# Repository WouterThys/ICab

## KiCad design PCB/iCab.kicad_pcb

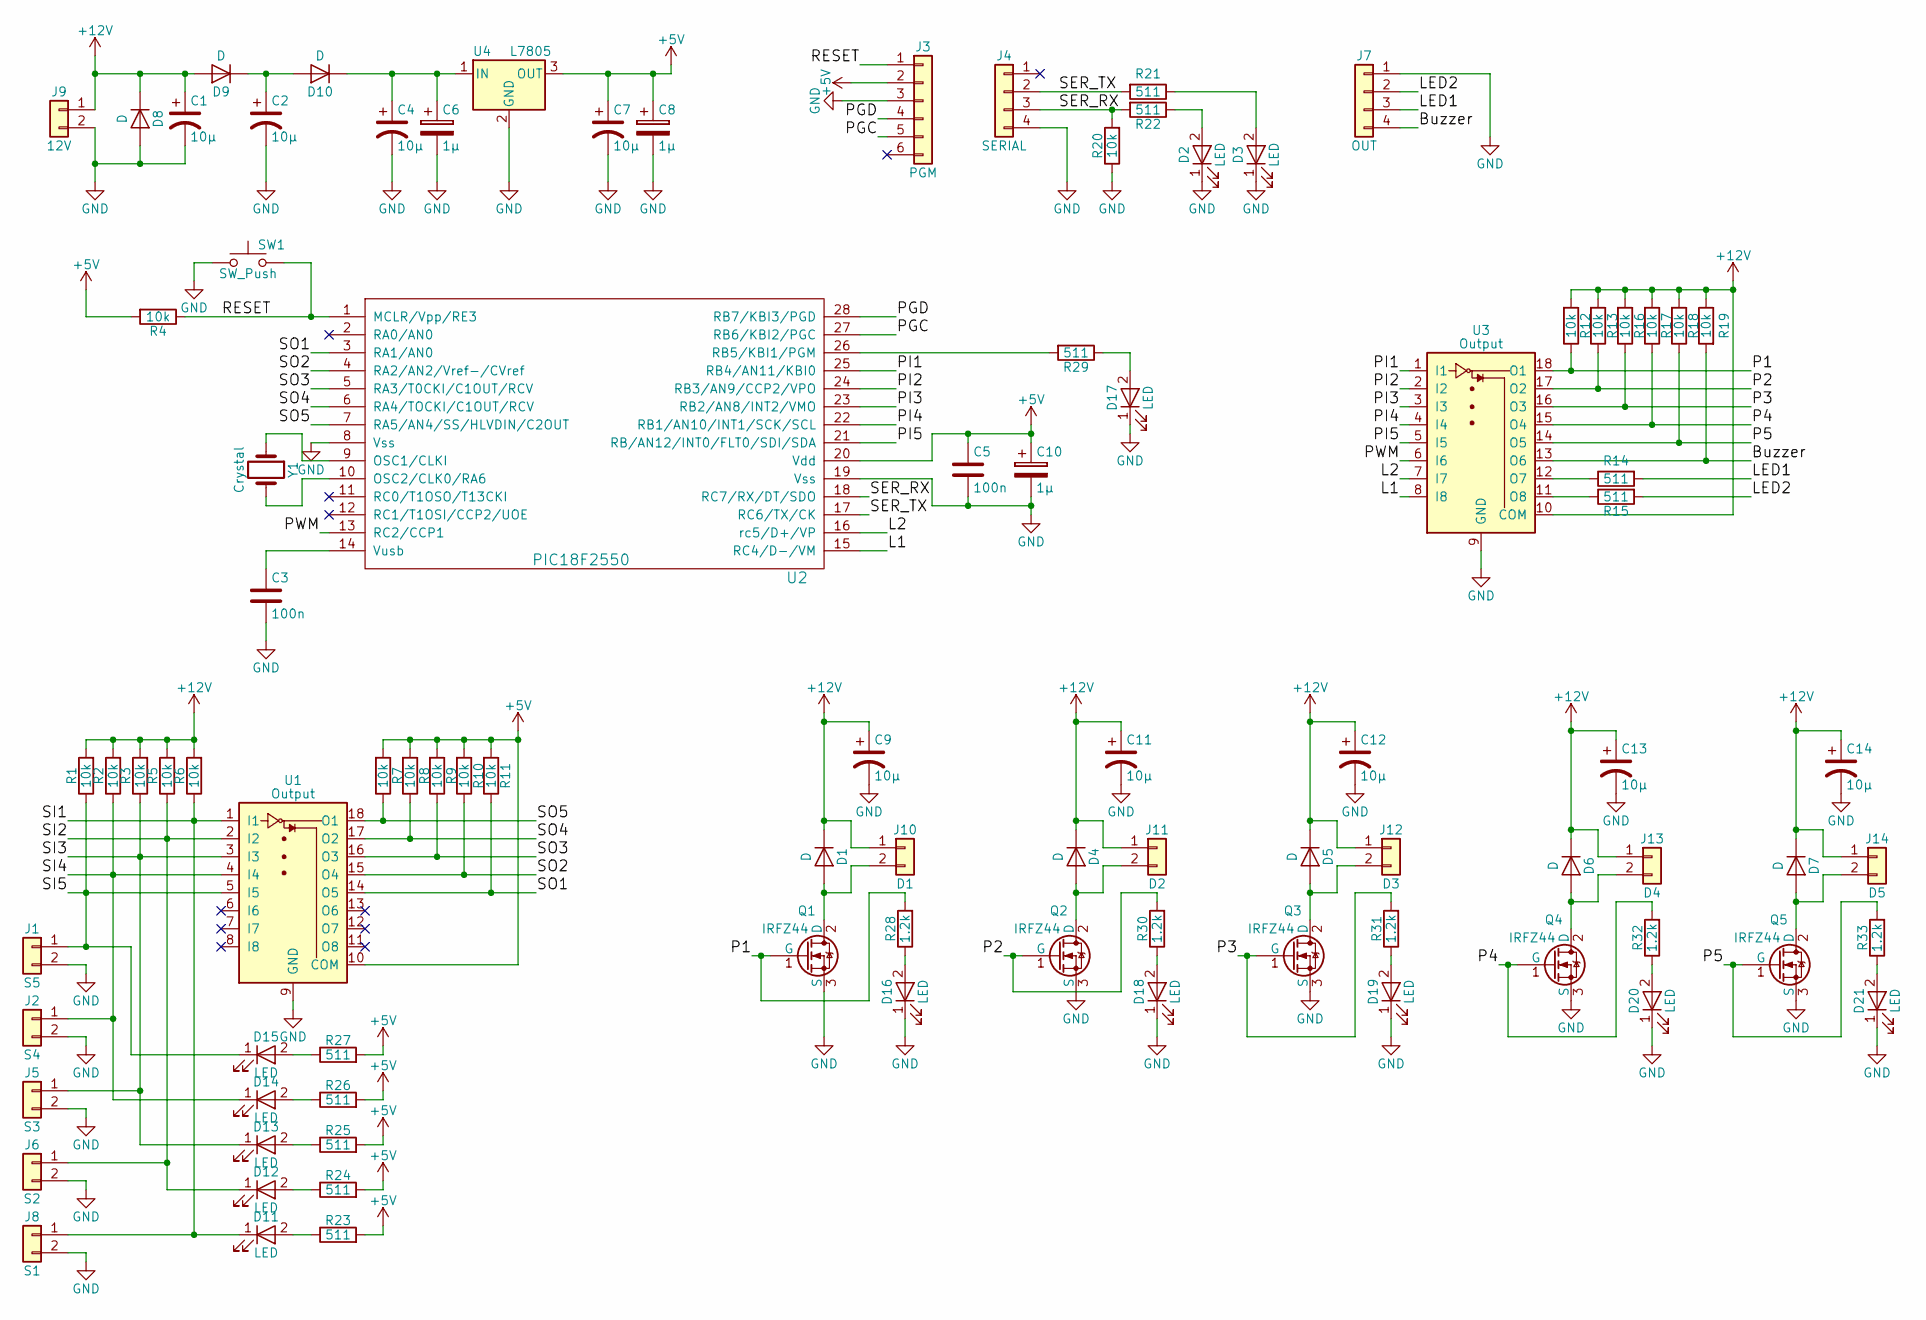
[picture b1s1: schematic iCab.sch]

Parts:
C1, C2, C4, C7, C9, C11, C12, C13, C14: 10µ; CP_Radial_D5.0mm_P2.00mm
C3, C5: 100n; C_0603_HandSoldering
C6, C8, C10: 1µ; CP_Tantalum_Case-A_EIA-3216-18_Reflow
D1, D4, D5, D6, D7: D; D_T-1_P5.08mm_Horizontal
D2, D3, D11, D12, D13, D14, D15, D16, D17, D18, D19, D20, D21: LED; LED_0603_HandSoldering
D8, D9, D10: D; D_T-1_P10.16mm_Horizontal
J1: S5; TerminalBlock_Phoenix_MKDS-1,5-2_1x02_P5.00mm_Horizontal
J2: S4; TerminalBlock_Phoenix_MKDS-1,5-2_1x02_P5.00mm_Horizontal
J3: PGM; Pin_Header_Straight_1x06_Pitch2.54mm
J4: SERIAL; Molex_PicoBlade_53047-0410_04x1.25mm_Straight
J5: S3; TerminalBlock_Phoenix_MKDS-1,5-2_1x02_P5.00mm_Horizontal
J6: S2; TerminalBlock_Phoenix_MKDS-1,5-2_1x02_P5.00mm_Horizontal
J7: OUT; Molex_PicoBlade_53047-0410_04x1.25mm_Straight
J8: S1; TerminalBlock_Phoenix_MKDS-1,5-2_1x02_P5.00mm_Horizontal
J9: 12V; TerminalBlock_Phoenix_MKDS-1,5-2_1x02_P5.00mm_Horizontal
J10: D1; TerminalBlock_Phoenix_MKDS-1,5-2_1x02_P5.00mm_Horizontal
J11: D2; TerminalBlock_Phoenix_MKDS-1,5-2_1x02_P5.00mm_Horizontal
J12: D3; TerminalBlock_Phoenix_MKDS-1,5-2_1x02_P5.00mm_Horizontal
J13: D4; TerminalBlock_Phoenix_MKDS-1,5-2_1x02_P5.00mm_Horizontal
J14: D5; TerminalBlock_Phoenix_MKDS-1,5-2_1x02_P5.00mm_Horizontal
Q1, Q2, Q3, Q4, Q5: IRFZ44; TO-220_Vertical
R1, R2, R3, R4, R5, R6, R7, R8, R9, R10, R11, R12, R13, R16, R17, R18, R19, R20: 10k; R_0603_HandSoldering
R14, R15, R21, R22, R23, R24, R25, R26, R27, R29: 511; R_0603_HandSoldering
R28, R30, R31, R32, R33: 1.2k; R_0603_HandSoldering
SW1: SW_Push; SW_PUSH_6mm
U1, U3: Output; DIP-18_W7.62mm
U2: PIC18F2550; DIP-28_W7.62mm
U4: L7805; TO-220_Vertical
Y1: Crystal; Crystal_HC49-U_Vertical

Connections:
+5V: C5.1, C7.1, C8.1, C10.1, J3.2, R4.2, R7.2, R8.2, R9.2, R10.2, R11.2, R23.2, R24.2, R25.2, R26.2, R27.2, U1.10 (COM), U2.20 (Vdd), U4.3 (OUT); also elsewhere on the board
+12V: C1.1, C9.1, C11.1, C12.1, C13.1, C14.1, D1.1 (K), D4.1 (K), D5.1 (K), D6.1 (K), D7.1 (K), D8.1 (K), D9.2 (A), J9.1, J10.1, J11.1, J12.1, J13.1, J14.1, R1.2, R2.2, R3.2, R5.2, R6.2, R12.2, R13.2, R16.2, R17.2, R18.2, R19.1, U3.10 (COM); also elsewhere on the board
/Buzzer: J7.4, R19.2, U3.13 (O6); also elsewhere on the board
/L1: U2.15 (RC4/D-/VM), U3.8 (I8)
/L2: U2.16 (rc5/D+/VP), U3.7 (I7)
/LED1: J7.3, R14.2; also elsewhere on the board
/LED2: J7.2, R15.2; also elsewhere on the board
/P1: Q1.1 (G), R12.1, R28.2, U3.18 (O1)
/P3: Q3.1 (G), R16.1, R31.2, U3.16 (O3)
/P4: Q4.1 (G), R17.1, R32.2, U3.15 (O4)
/P5: Q5.1 (G), R18.1, R33.2, U3.14 (O5)
/PGC: J3.5, U2.27 (RB6/KBI2/PGC); also elsewhere on the board
/PGD: J3.4, U2.28 (RB7/KBI3/PGD); also elsewhere on the board
/PI1: U2.25 (RB4/AN11/KBI0), U3.1 (I1)
/PI2: U2.24 (RB3/AN9/CCP2/VPO), U3.2 (I2)
/PI3: U2.23 (RB2/AN8/INT2/VMO), U3.3 (I3)
/PI4: U2.22 (RB1/AN10/INT1/SCK/SCL), U3.4 (I4)
/PI5: U2.21 (RB/AN12/INT0/FLT0/SDI/SDA), U3.5 (I5)
/PWM: U2.13 (RC2/CCP1), U3.6 (I6)
/RESET: J3.1, R4.1, SW1.2, U2.1 (MCLR/Vpp/RE3); also elsewhere on the board
/SER_RX: J4.3, R20.2, R22.2, U2.18 (RC7/RX/DT/SDO); also elsewhere on the board
/SER_TX: J4.2, R21.2, U2.17 (RC6/TX/CK); also elsewhere on the board
/SI1: D11.1 (K), J8.1, R6.1, U1.1 (I1)
/SI2: D12.1 (K), J6.1, R5.1, U1.2 (I2)
/SI3: D13.1 (K), J5.1, R3.1, U1.3 (I3)
/SI4: D14.1 (K), J2.1, R2.1, U1.4 (I4)
/SI5: D15.1 (K), J1.1, R1.1, U1.5 (I5)
/SO1: R11.1, U1.14 (O5), U2.3 (RA1/AN0)
/SO2: R10.1, U1.15 (O4), U2.4 (RA2/AN2/Vref-/CVref)
/SO3: R9.1, U1.16 (O3), U2.5 (RA3/T0CKI/C1OUT/RCV)
/SO4: R8.1, U1.17 (O2), U2.6 (RA4/TOCKI/C1OUT/RCV)
/SO5: R7.1, U1.18 (O1), U2.7 (RA5/AN4/SS/HLVDIN/C2OUT)
unnamed: C2.1, D9.1 (K), D10.2 (A)
unnamed: C3.1, U2.14 (Vusb)
unnamed: C4.1, C6.1, D10.1 (K), U4.1 (IN)
unnamed: D1.2 (A), J10.2, Q1.2 (D)
unnamed 36: D2.2 (A), R22.1; also elsewhere on the board
unnamed 37: D3.2 (A), R21.1; also elsewhere on the board
unnamed: D4.2 (A), J11.2, Q2.2 (D)
unnamed: D5.2 (A), J12.2, Q3.2 (D)
unnamed: D6.2 (A), J13.2, Q4.2 (D)
unnamed: D7.2 (A), J14.2, Q5.2 (D)
unnamed: D11.2 (A), R23.1
unnamed: D12.2 (A), R24.1
unnamed: D13.2 (A), R25.1
unnamed: D14.2 (A), R26.1
unnamed: D15.2 (A), R27.1
unnamed: D16.2 (A), R28.1
unnamed: D17.2 (A), R29.1
unnamed: D18.2 (A), R30.1
unnamed: D19.2 (A), R31.1
unnamed: D20.2 (A), R32.1
unnamed: D21.2 (A), R33.1
unnamed: R14.1, U3.12 (O7)
unnamed: R15.1, U3.11 (O8)
unnamed: R29.2, U2.26 (RB5/KBI1/PGM)
unnamed 56: U2.9 (OSC1/CLKI), Y1.1; also elsewhere on the board
unnamed 57: U2.10 (OSC2/CLK0/RA6), Y1.2; also elsewhere on the board

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
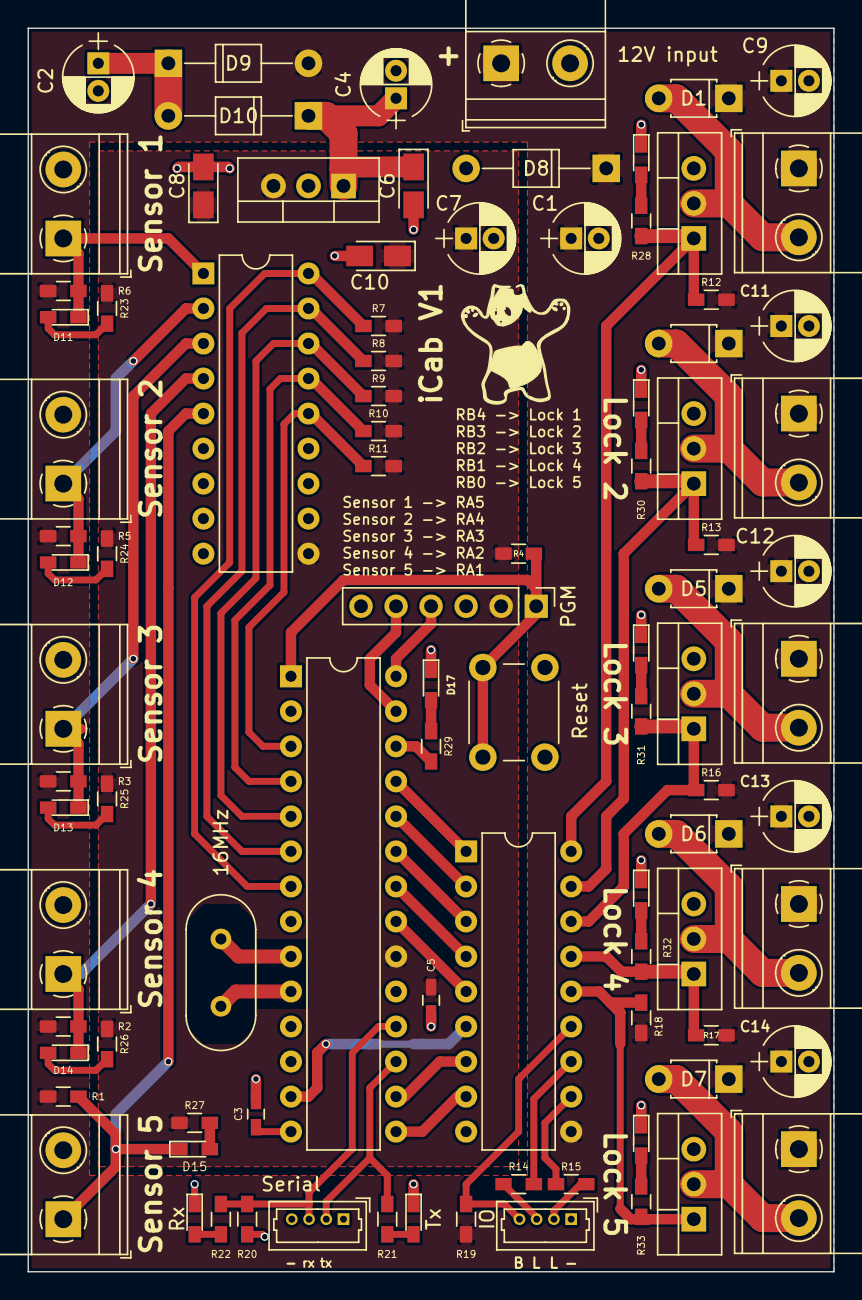
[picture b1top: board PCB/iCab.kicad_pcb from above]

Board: 2 copper layers, 58.4 x 90.2 mm, 93 parts (0 on the bottom side), 60 nets.

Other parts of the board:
12V input: 12V; TerminalBlock_Phoenix_MKDS-1,5-2_1x02_P5.00mm_Horizontal
16MHz: Crystal; Crystal_HC49-U_Vertical
IO: OUT; Molex_PicoBlade_53047-0410_04x1.25mm_Straight
PGM: PGM; Pin_Header_Straight_1x06_Pitch2.54mm
Reset: SW_Push; SW_PUSH_6mm
Rx: LED; LED_0603_HandSoldering
Serial: SERIAL; Molex_PicoBlade_53047-0410_04x1.25mm_Straight
Tx: LED; LED_0603_HandSoldering

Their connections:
+5V: PGM.2; also elsewhere on the board
+12V: 12V input.1; also elsewhere on the board
/Buzzer: IO.4; also elsewhere on the board
/LED1: IO.3; also elsewhere on the board
/LED2: IO.2; also elsewhere on the board
/PGC: PGM.5; also elsewhere on the board
/PGD: PGM.4; also elsewhere on the board
/RESET: PGM.1, Reset.2; also elsewhere on the board
/SER_RX: Serial.3; also elsewhere on the board
/SER_TX: Serial.2; also elsewhere on the board
unnamed 36: Rx.2; also elsewhere on the board
unnamed 37: Tx.2; also elsewhere on the board
unnamed 56: 16MHz.1; also elsewhere on the board
unnamed 57: 16MHz.2; also elsewhere on the board

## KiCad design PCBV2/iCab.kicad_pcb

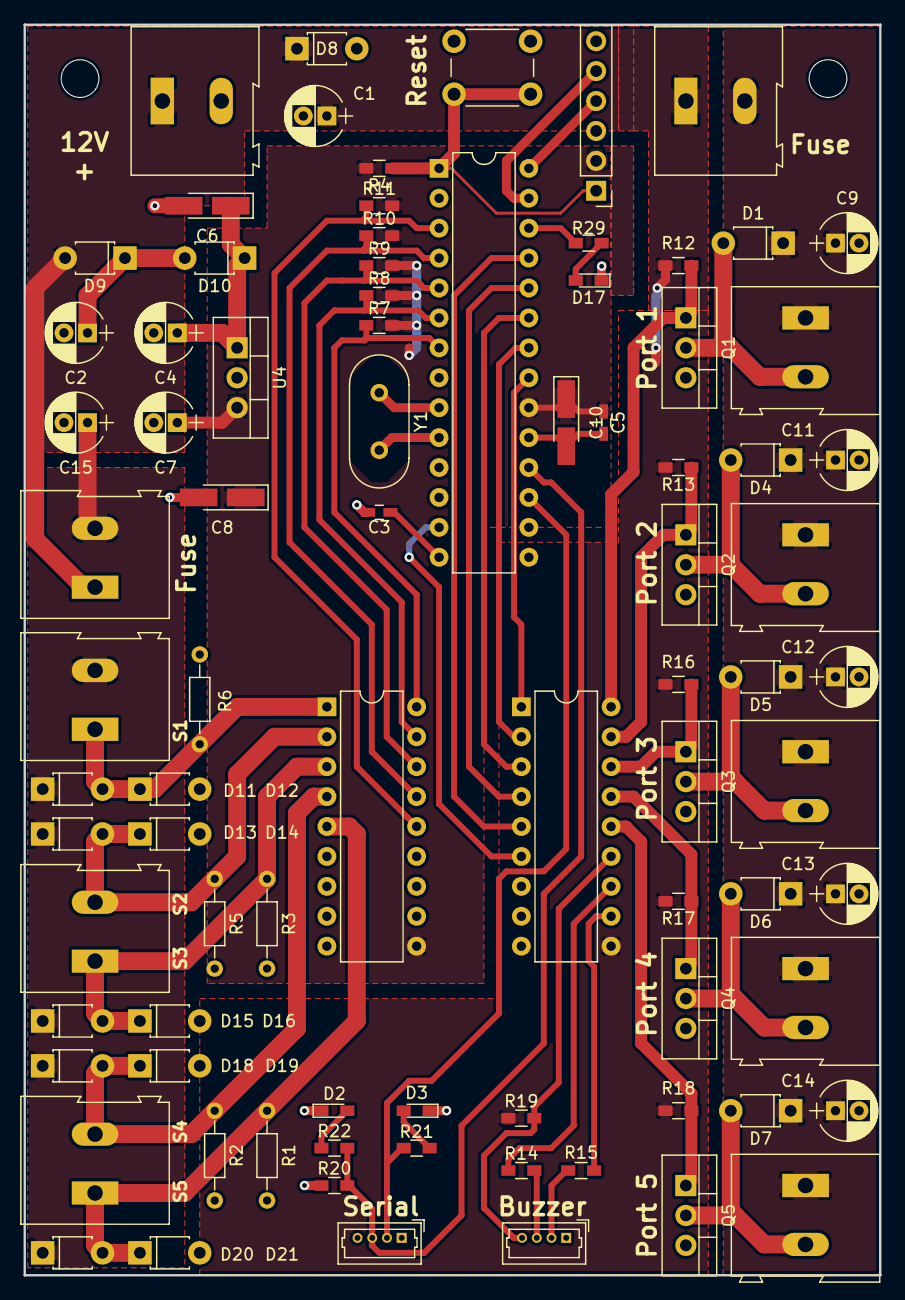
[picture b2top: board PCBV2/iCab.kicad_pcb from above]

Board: 2 copper layers, 72.6 x 106.2 mm, 86 parts (0 on the bottom side), 50 nets.

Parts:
C1, C2, C4, C7, C9, C11, C12, C13, C14, C15: 10µ; CP_Radial_D5.0mm_P2.00mm
C3, C5: 100n; C_0603_HandSoldering
C6, C8, C10: 1µ; CP_Tantalum_Case-A_EIA-3216-18_Hand
D1, D4, D5, D6, D7, D8, D9, D10, D11, D12, D13, D14, D15, D16, D18, D19, D20, D21: D; D_T-1_P5.08mm_Horizontal
D2, D3, D17: LED; LED_0603_HandSoldering
H1, H2: MountingHole; MountingHole_3.2mm_M3
J1, J8, J15: S5; TerminalBlock_Altech_AK300-2_P5.00mm
J2: S4; TerminalBlock_Altech_AK300-2_P5.00mm
J3: PGM; Pin_Header_Straight_1x06_Pitch2.54mm
J4: SERIAL; Molex_PicoBlade_53047-0410_04x1.25mm_Straight
J5: S3; TerminalBlock_Altech_AK300-2_P5.00mm
J7: OUT; Molex_PicoBlade_53047-0410_04x1.25mm_Straight
J9: 12V; TerminalBlock_Altech_AK300-2_P5.00mm
J10: D1; TerminalBlock_Altech_AK300-2_P5.00mm
J11: D2; TerminalBlock_Altech_AK300-2_P5.00mm
J12: D3; TerminalBlock_Altech_AK300-2_P5.00mm
J13: D4; TerminalBlock_Altech_AK300-2_P5.00mm
J14: D5; TerminalBlock_Altech_AK300-2_P5.00mm
Q1, Q2, Q3, Q4, Q5: IRFZ44; TO-220-3_Vertical
R1, R2, R3, R5, R6: 100k; R_Axial_DIN0204_L3.6mm_D1.6mm_P7.62mm_Horizontal
R4, R7, R8, R9, R10, R11, R12, R13, R16, R17, R18, R19, R20: 10k; R_0603_HandSoldering
R14, R15, R21, R22, R29: 511; R_0603_HandSoldering
SW1: SW_Push; SW_PUSH_6mm
U1, U3: Output; DIP-18_W7.62mm
U2: PIC18F2550; DIP-28_W7.62mm
U4: L7805; TO-220-3_Vertical
Y1: Crystal; Crystal_HC49-U_Vertical

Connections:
+5V: C5.1, C7.1, C8.1, C10.1, J3.2, R4.2, R7.2, R8.2, R9.2, R10.2, R11.2, U1.10, U2.20, U4.3
+12V: C1.1, D8.1, D9.2, J8.1, J9.1, J15.1, R12.2, R13.2, R16.2, R17.2, R18.2, R19.1, U3.10
/Buzzer: J7.4, R19.2, U3.13
/LED1: J7.3, R14.2
/LED2: J7.2, R15.2
/P1: Q1.1, R12.1, U3.18
/P2: Q2.1, R13.1, U3.17
/P3: Q3.1, R16.1, U3.16
/P4: Q4.1, R17.1, U3.15
/P5: Q5.1, R18.1, U3.14
/PGC: J3.5, U2.27
/PGD: J3.4, U2.28
/PI1: U2.21, U3.1
/PI2: U2.22, U3.2
/PI3: U2.23, U3.3
/PI4: U2.24, U3.4
/PI5: U2.25, U3.5
/PWM: U2.13, U3.6
/RESET: J3.1, R4.1, SW1.2, U2.1
/SER_RX: J4.3, R20.2, R22.2, U2.18
/SER_TX: J4.2, R21.2, U2.17
/SI1: D11.2, D12.1, J5.1, R6.1, U1.1
/SI2: D13.2, D14.1, J2.2, R5.1, U1.2
/SI3: D15.2, D16.1, J2.1, R3.1, U1.3
/SI4: D18.2, D19.1, J1.2, R2.1, U1.4
/SI5: D20.2, D21.1, J1.1, R1.1, U1.5
/SO1: R11.1, U1.14, U2.3
/SO2: R10.1, U1.15, U2.4
/SO3: R9.1, U1.16, U2.5
/SO4: R8.1, U1.17, U2.6
/SO5: R7.1, U1.18, U2.7
GND: C1.2, C2.2, C3.2, C4.2, C5.2, C6.2, C7.2, C8.2, C9.2, C10.2, C11.2, C12.2, C13.2, C14.2, C15.2, D2.1, D3.1, D8.2, D12.2, D14.2, D16.2, D17.1, D19.2, D21.2, J3.3, J4.4, J7.1, J9.2, Q1.3, Q2.3, Q3.3, Q4.3, Q5.3, R1.2, R2.2, R3.2, R5.2, R6.2, R20.1, SW1.1, U1.9, U2.8, U2.19, U3.9, U4.2
unnamed: C2.1, D9.1, D10.2
unnamed: C3.1, U2.14
unnamed: C4.1, C6.1, D10.1, U4.1
unnamed: C9.1, C11.1, C12.1, C13.1, C14.1, D1.1, D4.1, D5.1, D6.1, D7.1, J10.1, J11.1, J12.1, J13.1, J14.1, J15.2
unnamed: C15.1, D11.1, D13.1, D15.1, D18.1, D20.1, J5.2, J8.2
unnamed: D1.2, J10.2, Q1.2
unnamed: D2.2, R22.1
unnamed: D3.2, R21.1
unnamed: D4.2, J11.2, Q2.2
unnamed: D5.2, J12.2, Q3.2
unnamed: D6.2, J13.2, Q4.2
unnamed: D7.2, J14.2, Q5.2
unnamed: D17.2, R29.1
unnamed: R14.1, U3.12
unnamed: R15.1, U3.11
unnamed: R29.2, U2.26
unnamed: U2.9, Y1.1
unnamed: U2.10, Y1.2

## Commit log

2017-11-22 creation
2017-11-22 ignore file
2017-11-22 create main and main application
2017-11-22 started programming!!
2017-11-23 first web call success!!
2017-11-23 first attempt to fetch users
2017-11-23 Added a lot
2017-11-23 Key pad stuff
2017-11-24 Added new c project
2017-11-25 Created door controller
2017-11-25 Writing to uart if change, reading from uart
2017-11-25 Created controller and timer fsm
2017-11-25 reinité
2017-11-25 much commit
2017-11-26 serial manager and logs
2017-11-26 rebuild pic project
2017-11-27 logging and keypad
2017-11-27 work work work
2017-11-27 user log in
2017-11-27 inventory panel
2017-11-27 timer
2017-11-28 logging in and off a user
2017-11-28 new icons
2017-12-01 update web service
2017-12-02 test commit
2018-03-12 test
2018-03-12 alarm in hardware + close logic
2018-03-31 PWM driver for alarm stuff
2018-03-31 before pcb pull
2018-03-31 added pcb to project
2018-04-01 c xml
2018-04-01 new pcb
2018-04-14 update pcb references
2018-04-14 clean up hw, clean up logs panel
2018-04-14 reading items
2018-04-22 finetuning
2018-04-27 screen resolution layout
2018-05-01 build pic
2018-05-06 getting ready for production
2018-05-06 added password for settings dialog
2018-05-28 properties
2018-05-29 extra user options
2018-06-07 md5 encryption done wright
2018-06-07 CanStopTimer
2018-06-29 iCab stopping timer and stuff
2019-02-01 pcb v2
2019-02-01 some stuff
2019-02-03 pcb2
2019-02-12 clean up and test PCBV2
2019-04-16 build 16/04/2019 icab
